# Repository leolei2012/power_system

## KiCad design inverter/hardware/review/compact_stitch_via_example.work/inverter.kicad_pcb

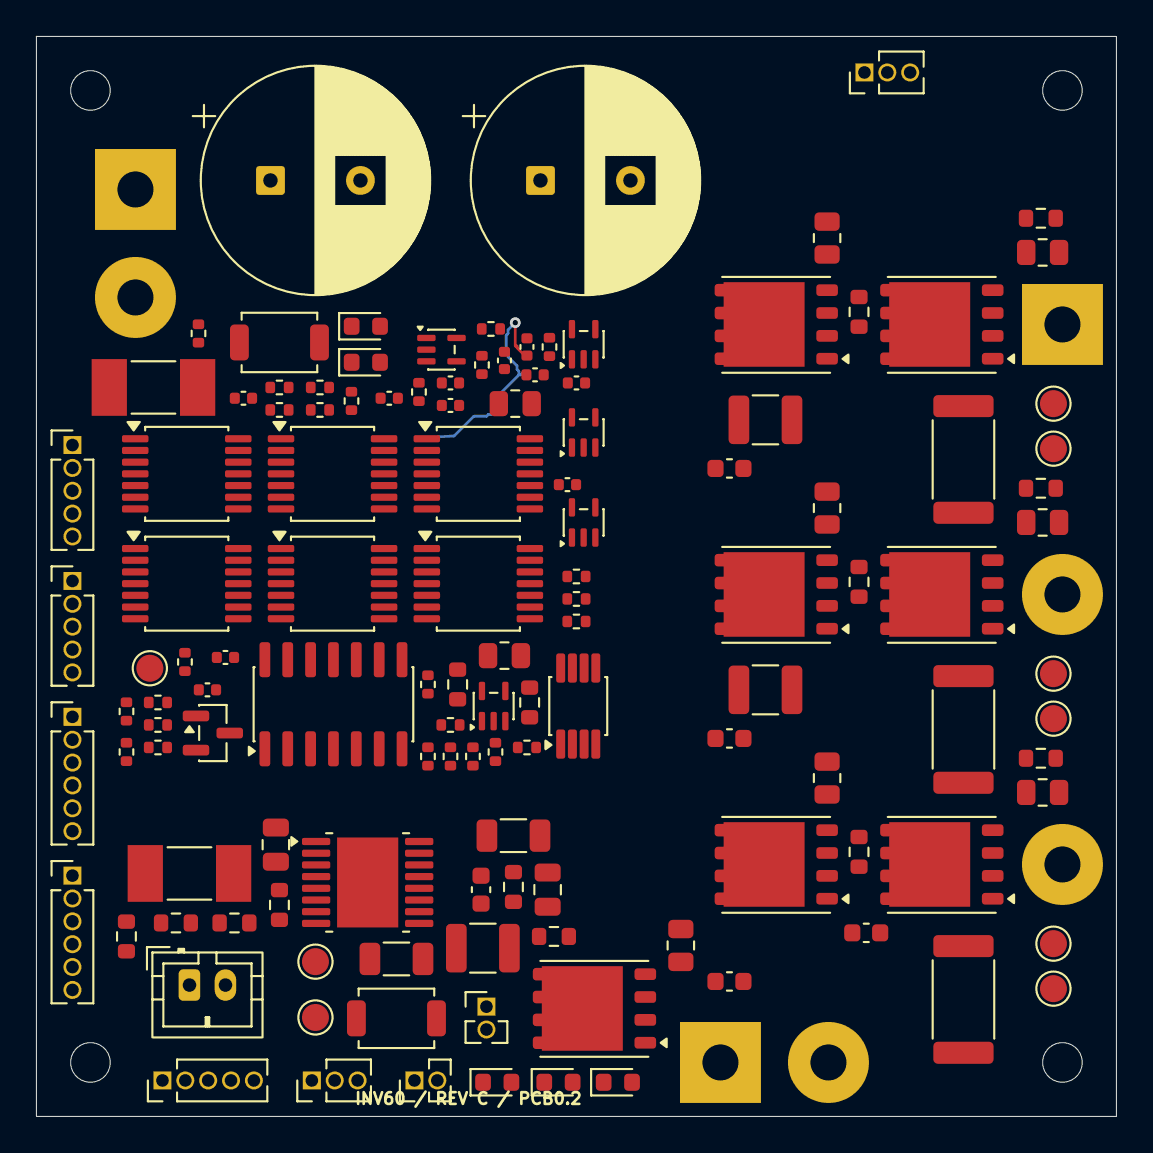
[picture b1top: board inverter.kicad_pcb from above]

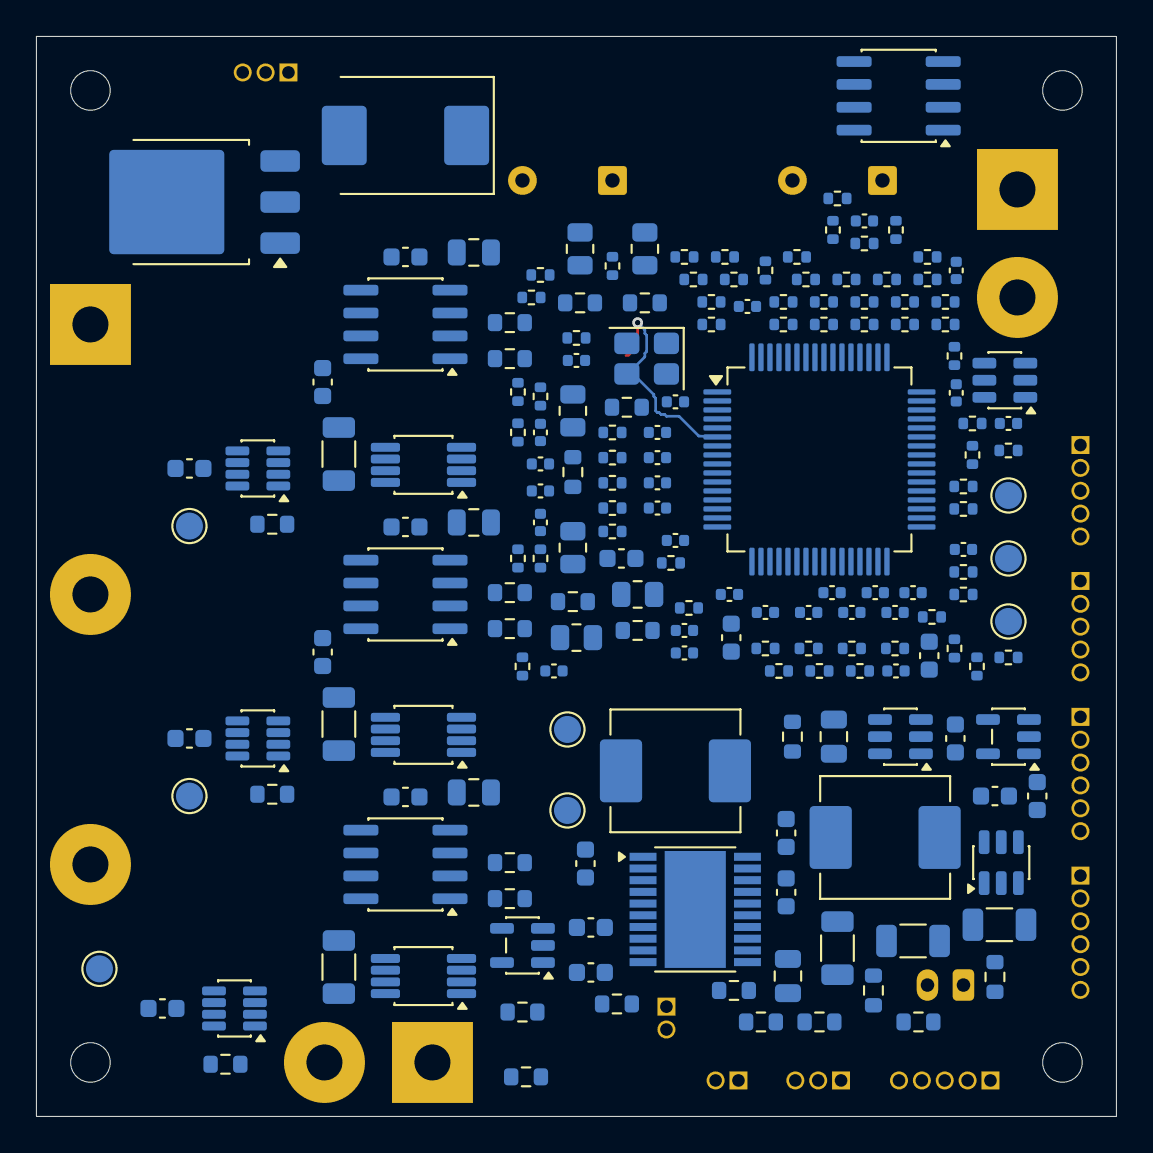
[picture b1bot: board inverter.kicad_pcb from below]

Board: 6 copper layers, 60.0 x 60.0 mm, 317 parts (183 on the bottom side), 209 nets.

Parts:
C1: 1u; C_0805_2012Metric
C2: 22n; C_0603_1608Metric
C3, C6, C11: 10u; C_1206_3216Metric
C4, C5, C9, C12, C24, C26, C28, C30, C32, C34, C36, C37, C38, C39, C51, C52, C53: 100n; C_0603_1608Metric
C7: 470n; C_0805_2012Metric
C8: 22u; C_1210_3225Metric
C10, C27, C31, C35: 4.7u; C_0805_2012Metric
C13, C14: 22u; C_1206_3216Metric
C15, C23, C78, C80: 1u; C_0603_1608Metric
C16: 2.2u; C_0603_1608Metric
C17, C40, C41, C43, C45, C47, C49, C54, C56, C57, C58, C59, C60, C61, C62, C63, C64, C65, C66, C67, C77, C79, C81, C82: 100n; C_0402_1005Metric
C18: 10u; C_0805_2012Metric
C19, C20: 220u / 100V; CP_Radial_D12.5mm_H25mm_P5.00mm
C21, C22: 2.2u / 100V X7R; C_1210_3225Metric
C25, C29, C33: 2.2u; C_1206_3216Metric
C42: 100p; C_0402_1005Metric
C44, C46, C48, C69, C70, C71, C72, C73, C74, C75, C76: 1n; C_0402_1005Metric
C50, C55: 10n; C_0402_1005Metric
C68: 4.7u; C_0603_1608Metric
C83, C84: 18p / provisional; C_0402_1005Metric
D1: MBRD20150CT-13; TO-252-3_TabPin2
D2: SMCJ60CA / CANDIDATE DNP; D_SMC
D3: PWR; LED_0603_1608Metric
D4: LED_RUN; LED_0603_1608Metric
D5: LED_FAULT; LED_0603_1608Metric
D6: LED_COMM; LED_0603_1608Metric
D7: LED_AUX; LED_0603_1608Metric
F1: 0476015.MRSN; Fuse_Littelfuse-NANO2-451_453
F2: 0451002.MRL; Fuse_Littelfuse-NANO2-451_453
H1, H2, H3, H4: MountingHole_2.2mm_M2
J2: AUX: +12..24V / GND; JST_PH_B2B-PH-K_1x02_P2.00mm_Vertical
J3: DC INPUT: + / -; WireSolder_2P_P6.00mm_D2.00mm
J4: RAW PWM: U / V / W; WireSolder_3P_P15.00mm_D2.00mm
J5: BRAKE POWER: BR+ / BR_SW; WireSolder_2P_P6.00mm_D2.00mm
J7: OPTIONAL SENSOR 5V / GND; PinHeader_HCTL_PZ127_1x02_P1.27mm_D0.70mm
J8: EXTERNAL 10k NTC; PinHeader_HCTL_PZ127_1x02_P1.27mm_D0.70mm
J9: ENC_A: PWR GND A B Z; PinHeader_HCTL_PZ127_1x05_P1.27mm_D0.70mm
J10: ENC_B: PWR GND A B Z; PinHeader_HCTL_PZ127_1x05_P1.27mm_D0.70mm
J11: SPI_A: PWR GND SCK MOSI MISO CS; PinHeader_HCTL_PZ127_1x06_P1.27mm_D0.70mm
J12: SPI_B: PWR GND SCK MOSI MISO CS; PinHeader_HCTL_PZ127_1x06_P1.27mm_D0.70mm
J13: SWD: VTREF IO CLK GND NRST; PinHeader_HCTL_PZ127_1x05_P1.27mm_D0.70mm
J14: TTL: TX RX GND; PinHeader_HCTL_PZ127_1x03_P1.27mm_D0.70mm
J15: CAN: H L GND; PinHeader_HCTL_PZ127_1x03_P1.27mm_D0.70mm
L1, L2: 4.7uH; L_Sunlord_MWSA0603S
Q1, Q2, Q3, Q4, Q5, Q6, Q7: BSC110N15NS5; BSC110N15NS5_TDSON8_8PhysicalPins
Q8: MMBT3904LT1G; SOT-23
R1: 78.7k; R_0603_1608Metric
R2, R4, R7, R10, R11, R15, R16, R18, R21, R22, R23, R24, R27, R28, R29, R30, R33, R34, R35, R36, R50, R51, R55, R56, R60, R61, R65, R66: 10k; R_0603_1608Metric
R3: 221k; R_0603_1608Metric
R5: 402k; R_0603_1608Metric
R6: 7.87k; R_0603_1608Metric
R8, R9: 100k; R_0603_1608Metric
R12: 20k; R_0603_1608Metric
R13, R40, R41, R44, R45, R70, R72, R73, R74, R76, R77, R78, R79, R80, R81, R82, R95, R97, R99, R102, R104, R106, R112, R118, R122, R125, R128, R143: 10k; R_0402_1005Metric
R14: 49.9k; R_0603_1608Metric
R17, R19, R20, R25, R26, R31, R32: 15; R_0805_2012Metric
R37, R38, R39: 47; R_0603_1608Metric
R42, R47: 39k; R_0402_1005Metric
R43, R46: 1.8k; R_0402_1005Metric
R48, R49, R53, R54, R58, R59, R63, R64: 240k; R_0805_2012Metric
R52, R57, R62, R67: 47; R_0402_1005Metric
R68: 20k; R_0402_1005Metric
R69: 13k; R_0402_1005Metric
R71: 76.1k; R_0402_1005Metric
R75, R83: 100k; R_0402_1005Metric
R84, R85, R86, R87, R88, R89, R90, R91, R94, R96, R98, R101, R103, R105, R124: 100; R_0402_1005Metric
R92, R93, R100, R107, R113, R119, R126, R127: 0; R_0402_1005Metric
R108, R109, R110, R111, R114, R115, R116, R117, R120, R121, R123, R135, R136, R137, R138, R139, R140, R141, R142: 33; R_0402_1005Metric
R129: 120; R_0402_1005Metric
R130, R131, R132, R133, R134: 2.2k; R_0402_1005Metric
RS1, RS2, RS3: 5m / 3W / 1%; R_2512_6332Metric
SW1: AUX_RESET; SW_SPST_TS-1088-xR020
SW2: MCU_RESET; SW_SPST_TS-1088-xR020
TP1: +12V_DRV; TestPoint_Pad_D1.5mm
TP2: BB_VREG; TestPoint_Pad_D1.5mm
TP3: DRV_PG_LOGIC; TestPoint_Pad_D1.5mm
TP4: SENSOR_PWR_FLT_N; TestPoint_Pad_D1.5mm
TP5: U_PHASE; TestPoint_Pad_D1.5mm
TP6: U_SOURCE; TestPoint_Pad_D1.5mm
TP7: V_PHASE; TestPoint_Pad_D1.5mm
TP8: V_SOURCE; TestPoint_Pad_D1.5mm
TP9: W_PHASE; TestPoint_Pad_D1.5mm
TP10: W_SOURCE; TestPoint_Pad_D1.5mm
TP11: I_U; TestPoint_Pad_D1.5mm
TP12: I_V; TestPoint_Pad_D1.5mm
TP13: I_W; TestPoint_Pad_D1.5mm
TP14: FAULT_LATCH; TestPoint_Pad_D1.5mm
TP15: BOOT0; TestPoint_Pad_D1.5mm
TP16: FAULT_N; TestPoint_Pad_D1.5mm
TP17: ENABLE_IN; TestPoint_Pad_D1.5mm
U1: TPS26600PWPR; HTSSOP-16-1EP_4.4x5mm_P0.65mm_EP3.4x5mm_Mask2.66x2.46mm
U2: TPS55165QPWPRQ1; TI_PWP0020W_HTSSOP-20_4.4x6.5mm_P0.65mm_EP2.79x3.64mm
U3: AP63205WU-7; TSOT-23-6
U4: TPS7A2033PDBVR; SOT-23-5
U5: TPS2553QDBVRQ1; SOT-23-6
U6: TPS3808G33DBVR; SOT-23-6
U7, U8, U9: 2ED2182S06FXUMA1; SOIC-8_3.9x4.9mm_P1.27mm
U10, U11, U12: INA241A1IDDFR; SOT-23-8
U13, U14, U15, U16, U17: TLV9001IDCKR; SOT-353_SC-70-5
U18, U19, U20, U21: TLV3202AIDGK; VSSOP-8_3x3mm_P0.65mm
U22, U23, U24, U25, U26: 74LVC08APW,118; TSSOP-14_4.4x5mm_P0.65mm
U27: 74LVC00APW,118; TSSOP-14_4.4x5mm_P0.65mm
U28: 74LVC74AD,118; SOIC-14_3.9x8.7mm_P1.27mm
U29: UCC27517DBVR; SOT-23-5
U30: STM32G431RBT6; LQFP-64_10x10mm_P0.5mm
U31: SN65HVD232DR; SOIC-8_3.9x4.9mm_P1.27mm
Y1: 8MHz / CL TBD / DNP; Crystal_SMD_3225-4Pin_3.2x2.5mm

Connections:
+3V3_A_MCU: C77.1, C78.1, R92.2, R93.1, U30.29
+3V3_INV: C16.1, C17.1, C37.1, C38.1, C39.1, C41.1, C43.1, C45.1, C47.1, C49.1, C51.1, C52.1, C53.1, C54.1, C56.1, C57.1, C58.1, C59.1, C60.1, C61.1, C62.1, C63.1, C64.1, C65.1, C66.1, C67.1, C68.1, C82.1, J13.1, R7.2, R13.2, R15.2, R40.1, R42.1, R45.1, R68.1, R70.1, R92.1, R95.2, R97.2, R99.2, R102.2, R104.2, R106.2, R112.2, R118.2, R125.2, R128.2, R130.1, R131.1, R132.1, R133.1, R134.1, R143.2, U4.5, U6.3, U6.5, U6.6, U10.6, U11.6, U12.6, U13.5, U14.5, U15.5, U16.5, U17.5, U18.8, U19.8, U20.8, U21.8, U22.14, U23.14, U24.14, U25.14, U26.14, U27.14, U28.1, U28.10, U28.13, U28.14, U30.1, U30.16, U30.32, U30.48, U30.64, U31.3
+5V_INV: C13.1, C14.1, C15.1, L2.2, R10.1, U3.1, U4.1, U4.3, U5.1, U5.3
+5V_SENSOR: C18.1, J7.1, R100.1, R107.1, R113.1, R119.1, U5.6
+12V_DRV: C8.1, C9.1, C23.1, C24.1, C27.1, C28.1, C31.1, C32.1, C35.1, C36.1, R71.1, TP1.1, U2.16, U2.17, U7.5, U8.5, U9.5, U29.1
/Analog protection/DRV_UV_DIV: R71.2, R72.1, U21.5
/Auxiliary input/AUX_DVDT: C2.1, U1.12
/Auxiliary input/AUX_FUSED: C1.1, F2.2, R1.1, R3.1, R8.1, U1.1, U1.2
/Auxiliary input/AUX_ILIM: R6.1, U1.11
/Auxiliary input/AUX_IN: F2.1, J2.1
/Auxiliary input/AUX_MODE: R5.1, U1.6
/Auxiliary input/AUX_OV_DIV: R3.2, R4.1, U1.5
/Auxiliary input/AUX_SHDN_N: R8.2, SW1.1, U1.7
/Auxiliary input/AUX_UV_DIV: R1.2, R2.1, U1.3
/Auxiliary input/EFUSE_RTN: C2.2, R2.2, R4.2, R5.2, R6.2, SW1.2, U1.8, U1.17
/Bus and brake/BR_DRV: R17.1, U29.5
/Bus and brake/BR_GATE: Q7.4, R17.2, R18.1
/Bus and brake/BR_SW: J5.2, Q7.5, Q7.6, Q7.7, Q7.8
/Bus and brake/DC_FUSED: D1.1, D1.3, F1.2
/Bus and brake/DC_INPUT_POS: F1.1, J3.1
/Current sensing/OC_HI_MID: R46.2, R47.1
/Current sensing/OC_LO_MID: R42.2, R43.1
/Current sensing/VBIAS_1V65: U10.3, U10.7, U11.3, U11.7, U12.3, U12.7, U13.3, U13.4
/Current sensing/VBIAS_DIV: C40.1, R40.2, R41.1, U13.1
/Debug and communication/CAN_H: J15.1, R129.1, U31.7
/Debug and communication/CAN_L: J15.2, R129.2, U31.6
/Debug and communication/CAN_RX_PHY: R127.1, U31.4
/Debug and communication/CAN_TX_PHY: R126.2, R128.1, U31.1
/Debug and communication/LED_AN_0: D3.2, R130.2
/Debug and communication/LED_AN_1: D4.2, R131.2
/Debug and communication/LED_AN_2: D5.2, R132.2
/Debug and communication/LED_AN_3: D6.2, R133.2
/Debug and communication/LED_AN_4: D7.2, R134.2
/Debug and communication/SWCLK_PORT: J13.3, R121.1
/Debug and communication/SWDIO_PORT: J13.2, R120.1
/Debug and communication/UART_RX_PORT: J14.2, R124.1
/Debug and communication/UART_TX_PORT: J14.1, R123.2
/Driver supply/BB_BST1: C4.1, U2.3
/Driver supply/BB_BST2: C5.1, U2.19
/Driver supply/BB_L1: C4.2, L1.1, U2.2
/Driver supply/BB_L2: C5.2, L1.2, U2.20
/Driver supply/BB_PG_DLY: R9.1, U2.10
/Driver supply/BB_VREG: C10.1, TP2.1, U2.11, U2.12, U2.14
/Driver supply/DRV_PG_NOM: R10.2, R11.1, U2.15
/Encoders and SPI/ENC_A_A_PORT: J9.3, R94.1
/Encoders and SPI/ENC_A_B_PORT: J9.4, R96.1
/Encoders and SPI/ENC_A_VCC: J9.1, R100.2
/Encoders and SPI/ENC_A_Z_PORT: J9.5, R98.1
/Encoders and SPI/ENC_B_A_PORT: J10.3, R101.1
/Encoders and SPI/ENC_B_B_PORT: J10.4, R103.1
/Encoders and SPI/ENC_B_VCC: J10.1, R107.2
/Encoders and SPI/ENC_B_Z_PORT: J10.5, R105.1
/Encoders and SPI/SPI_A_CS_PORT: J11.6, R111.2
/Encoders and SPI/SPI_A_MISO_PORT: J11.5, R110.2
/Encoders and SPI/SPI_A_MOSI_PORT: J11.4, R109.2
/Encoders and SPI/SPI_A_SCK_PORT: J11.3, R108.2
/Encoders and SPI/SPI_A_VCC: J11.1, R113.2
/Encoders and SPI/SPI_B_CS_PORT: J12.6, R117.2
/Encoders and SPI/SPI_B_MISO_PORT: J12.5, R116.2
/Encoders and SPI/SPI_B_MOSI_PORT: J12.4, R115.2
/Encoders and SPI/SPI_B_SCK_PORT: J12.3, R114.2
/Encoders and SPI/SPI_B_VCC: J12.1, R119.2
/Hardware latch/ENABLE_N: U24.10, U27.3
/Hardware latch/FAULT_ACTIVE: R74.1, U27.6
/Hardware latch/FAULT_BASE: Q8.1, R74.2, R75.1
/Hardware latch/FAULT_LATCH: TP14.1, U28.5
/Hardware latch/HEALTH_ALL: U24.6, U24.9, U24.12, U27.4, U28.4
/Hardware latch/HEALTH_CHAIN_1: U22.3, U22.4
/Hardware latch/HEALTH_CHAIN_2: U22.6, U22.9
/Hardware latch/HEALTH_CHAIN_3: U22.8, U22.12
/Hardware latch/HEALTH_CHAIN_4: U22.11, U23.1
/Hardware latch/HEALTH_CHAIN_5: U23.3, U23.4
/Hardware latch/HEALTH_CHAIN_6: U23.6, U23.9
/Hardware latch/HEALTH_CHAIN_7: U23.8, U23.12
/Hardware latch/HEALTH_CHAIN_8: U23.11, U24.1
/Hardware latch/HEALTH_CHAIN_9: U24.3, U24.4
/Hardware latch/HEALTH_UNLATCHED: U24.11, U25.1
/Hardware latch/NO_LATCH: U24.13, U27.5, U28.6
/Hardware latch/RESET_CLK: C55.1, R73.2, U28.3
/Hardware latch/RESET_REQUEST: R73.1, U24.8
/Logic and sensors/BUCK_BST: C12.1, U3.6
/Logic and sensors/BUCK_SW: C12.2, L2.1, U3.5
/Logic and sensors/SENSOR_ILIM: R14.1, U5.5
/Logic and sensors/SENSOR_PWR_FLT_N: R15.1, TP4.1, U5.4
/U half bridge/U_BOOT: C25.1, C26.1, U7.8
/U half bridge/U_GATE_H: Q1.4, R19.2, R21.1
/U half bridge/U_GATE_L: Q2.4, R20.2, R22.1
/U half bridge/U_HO: R19.1, U7.7
/U half bridge/U_LO: R20.1, U7.4
/V half bridge/V_BOOT: C29.1, C30.1, U8.8
/V half bridge/V_GATE_H: Q3.4, R25.2, R27.1
/V half bridge/V_GATE_L: Q4.4, R26.2, R28.1
/V half bridge/V_HO: R25.1, U8.7
/V half bridge/V_LO: R26.1, U8.4
/Voltage and NTC/V_DC_DIV: C42.1, R50.2, R51.1, U14.1
/Voltage and NTC/V_DC_DIV1: R48.2, R49.1
/Voltage and NTC/V_DC_DIV2: R49.2, R50.1
/Voltage and NTC/V_U: R57.1, U15.3, U15.4
/Voltage and NTC/V_U_DIV: C44.1, R55.2, R56.1, U15.1
/Voltage and NTC/V_U_DIV1: R53.2, R54.1
/Voltage and NTC/V_U_DIV2: R54.2, R55.1
/Voltage and NTC/V_V: R62.1, U16.3, U16.4
/Voltage and NTC/V_V_DIV: C46.1, R60.2, R61.1, U16.1
/Voltage and NTC/V_V_DIV1: R58.2, R59.1
/Voltage and NTC/V_V_DIV2: R59.2, R60.1
/Voltage and NTC/V_W: R67.1, U17.3, U17.4
/Voltage and NTC/V_W_DIV: C48.1, R65.2, R66.1, U17.1
/Voltage and NTC/V_W_DIV1: R63.2, R64.1
/Voltage and NTC/V_W_DIV2: R64.2, R65.1
/W half bridge/W_BOOT: C33.1, C34.1, U9.8
/W half bridge/W_GATE_H: Q5.4, R31.2, R33.1
/W half bridge/W_GATE_L: Q6.4, R32.2, R34.1
/W half bridge/W_HO: R31.1, U9.7
/W half bridge/W_LO: R32.1, U9.4
ADC_I_U: C69.1, R84.2, U30.8
ADC_I_V: C70.1, R85.2, U30.9
ADC_I_W: C71.1, R86.2, U30.10
ADC_TEMP_NTC: C76.1, R91.2, U30.26
ADC_V_DC: C72.1, R87.2, U30.11
ADC_V_U: C73.1, R88.2, U30.18
ADC_V_V: C74.1, R89.2, U30.24
ADC_V_W: C75.1, R90.2, U30.25
AUX_FLT_N: R7.1, U1.14, U24.5
AUX_PROTECTED: C3.1, C6.1, C7.1, C11.1, U1.15, U1.16, U2.4, U2.5, U2.6, U3.2, U3.3
BOOT0: R122.1, TP15.1, U30.61
BRAKE_IN: R16.1, R142.2, U29.3
BUS_OV_OK: U21.1, U23.5
CAN_RX: R127.2, U30.45
CAN_TX: R126.1, U30.46
DRIVE_PERMIT: R83.1, U25.3, U25.5, U25.10, U25.13, U26.2, U26.5, U26.10
DRV_PG_LOGIC: R11.2, R12.1, TP3.1, U24.2
DRV_UV_OK: U21.7, U23.10
ENABLE_IN: R82.1, R141.2, TP17.1, U25.2, U27.1, U27.2
ENC_A_A: R94.2, R95.1, U30.12
ENC_A_B: R96.2, R97.1, U30.13
ENC_A_Z: R98.2, R99.1, U30.14
ENC_B_A: R101.2, R102.1, U30.59
ENC_B_B: R103.2, R104.1, U30.60
ENC_B_Z: R105.2, R106.1, U30.17
FAULT_N: Q8.3, R143.1, TP16.1, U30.34
GND: C1.2, C3.2, C6.2, C7.2, C8.2, C9.2, C10.2, C11.2, C13.2, C14.2, C15.2, C16.2, C17.2, C18.2, C19.2, C20.2, C21.2, C22.2, C23.2, C24.2, C37.2, C38.2, C39.2, C40.2, C41.2, C42.2, C43.2, C44.2, C45.2, C46.2, C47.2, C48.2, C49.2, C50.2, C51.2, C52.2, C53.2, C54.2, C55.2, C56.2, C57.2, C58.2, C59.2, C60.2, C61.2, C62.2, C63.2, C64.2, C65.2, C66.2, C67.2, C68.2, C69.2, C70.2, C71.2, C72.2, C73.2, C74.2, C75.2, C76.2, C77.2, C78.2, C79.2, C80.2, C81.2, C82.2, C83.2, C84.2, D2.2, D3.1, J2.2, J3.2, J7.2, J8.2, J9.2, J10.2, J11.2, J12.2, J13.4, J14.3, J15.3, Q7.1, Q7.2, Q7.3, Q8.2, R9.2, R12.2, R14.2, R16.2, R18.2, R41.2, R44.2, R47.2, R51.2, R56.2, R61.2, R66.2, R69.2, R72.2, R75.2, R76.2, R77.2, R78.2, R79.2, R80.2, R81.2, R82.2, R83.2, R122.2, RS1.2, RS2.2, RS3.2, SW2.2, U1.9, U2.1, U2.7, U2.8, U2.9, U2.13, U2.18, U2.21, U3.4, U4.2, U5.2, U6.2, U10.1, U10.2, U10.4, U11.1, U11.2, U11.4, U12.1, U12.2, U12.4, U13.2, U14.2, U15.2, U16.2, U17.2, U18.4, U19.4, U20.4, U21.4, U22.7, U23.7, U24.7, U25.7, U26.7, U26.12, U26.13, U27.7, U27.9, U27.10, U27.12, U27.13, U28.2, U28.7, U28.11, U28.12, U29.2, U29.4, U30.15, U30.27, U30.31, U30.47, U30.63, U31.2, Y1.2, Y1.4
HSE_IN: C83.1, U30.5, Y1.1
HSE_OUT: C84.1, U30.6, Y1.3
I_U: R37.1, TP11.1, U10.5, U18.2, U18.5
I_U_PORT: R37.2, R84.1
I_V: R38.1, TP12.1, U11.5, U19.2, U19.5
I_V_PORT: R38.2, R85.1
I_W: R39.1, TP13.1, U12.5, U20.2, U20.5
I_W_PORT: R39.2, R86.1
LED_AUX: D7.1, U30.58
LED_COMM: D6.1, U30.55
LED_FAULT: D5.1, U30.40
LED_RUN: D4.1, U30.23
LOGIC_POWER_OK: C81.1, J13.5, R13.1, SW2.1, U6.1, U23.13, U30.7
MCU_BRAKE: R142.1, U30.38
MCU_ENABLE: R141.1, U30.22
MCU_PWM_UH: R135.1, U30.42
MCU_PWM_UL: R136.1, U30.35
MCU_PWM_VH: R137.1, U30.43
MCU_PWM_VL: R138.1, U30.36
MCU_PWM_WH: R139.1, U30.44
MCU_PWM_WL: R140.1, U30.37
OC_HIGH_REF: R45.2, R46.1, U18.3, U19.3, U20.3
OC_LOW_REF: R43.2, R44.1, U18.6, U19.6, U20.6
OC_U_HIGH_OK: U18.1, U22.1
OC_U_LOW_OK: U18.7, U22.2
OC_V_HIGH_OK: U19.1, U22.5
OC_V_LOW_OK: U19.7, U22.10
OC_W_HIGH_OK: U20.1, U22.13
OC_W_LOW_OK: U20.7, U23.2
OV_REF_1V30: R68.2, R69.1, U21.3, U21.6
PWM_UH_IN: R76.1, R135.2, U25.4
PWM_UL_IN: R77.1, R136.2, U25.9
PWM_VH_IN: R78.1, R137.2, U25.12
PWM_VL_IN: R79.1, R138.2, U26.1
PWM_WH_IN: R80.1, R139.2, U26.4
PWM_WL_IN: R81.1, R140.2, U26.9
SPI_A_CS: R111.1, R112.1, U30.51
SPI_A_MISO: R110.1, U30.20
SPI_A_MOSI: R109.1, U30.21
SPI_A_SCK: R108.1, U30.19
SPI_B_CS: R117.1, R118.1, U30.41
SPI_B_MISO: R116.1, U30.53
SPI_B_MOSI: R115.1, U30.54
SPI_B_SCK: R114.1, U30.52
SWCLK: R121.2, U30.50
SWDIO: R120.2, U30.49
TEMP_NTC: C50.1, J8.1, R70.2, R91.1
UART_RX: R124.2, R125.1, U30.33
UART_TX: R123.1, U30.30
U_HIN: R23.1, U7.1, U25.6
U_LIN: R24.1, U7.2, U25.8
U_PHASE: C25.2, C26.2, J4.1, Q1.1, Q1.2, Q1.3, Q2.5, Q2.6, Q2.7, Q2.8, R21.2, R53.1, TP5.1, U7.6
U_SOURCE: C27.2, C28.2, Q2.1, Q2.2, Q2.3, R22.2, R23.2, R24.2, RS1.1, TP6.1, U7.3, U10.8
VBUS: C19.1, C20.1, C21.1, C22.1, D1.2, D2.1, J5.1, Q1.5, Q1.6, Q1.7, Q1.8, Q3.5, Q3.6, Q3.7, Q3.8, Q5.5, Q5.6, Q5.7, Q5.8, R48.1
VREF_MCU: C79.1, C80.1, R93.2, U30.28
V_DC: R52.1, U14.3, U14.4, U21.2
V_DC_PORT: R52.2, R87.1
V_HIN: R29.1, U8.1, U25.11
V_LIN: R30.1, U8.2, U26.3
V_PHASE: C29.2, C30.2, J4.2, Q3.1, Q3.2, Q3.3, Q4.5, Q4.6, Q4.7, Q4.8, R27.2, R58.1, TP7.1, U8.6
V_SOURCE: C31.2, C32.2, Q4.1, Q4.2, Q4.3, R28.2, R29.2, R30.2, RS2.1, TP8.1, U8.3, U11.8
V_U_PORT: R57.2, R88.1
V_V_PORT: R62.2, R89.1
V_W_PORT: R67.2, R90.1
W_HIN: R35.1, U9.1, U26.6
W_LIN: R36.1, U9.2, U26.8
W_PHASE: C33.2, C34.2, J4.3, Q5.1, Q5.2, Q5.3, Q6.5, Q6.6, Q6.7, Q6.8, R33.2, R63.1, TP9.1, U9.6
W_SOURCE: C35.2, C36.2, Q6.1, Q6.2, Q6.3, R34.2, R35.2, R36.2, RS3.1, TP10.1, U9.3, U12.8

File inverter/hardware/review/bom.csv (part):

Reference,Value,Quantity,DNP,Sheet,Manufacturer,MPN,Supplier_PN,Purchase_URL,Footprint,Voltage_Rating,Tolerance,Design_Note,Selection_Status,Verification
C1,1u,1,no,/Auxiliary input/,YAGEO,TBD,,,Capacitor_SMD:C_0805_2012Metric,100V,,,value assigned; DC bias/MPN/LCSC pending,
C2,22n,1,no,/Auxiliary input/,YAGEO,TBD,,,Capacitor_SMD:C_0603_1608Metric,25V,,,value assigned; DC bias/MPN/LCSC pending,
C3,10u,1,no,/Auxiliary input/,YAGEO,TBD,,,Capacitor_SMD:C_1206_3216Metric,50V,,,value assigned; DC bias/MPN/LCSC pending,
F2,0451002.MRL,1,no,/Auxiliary input/,Littelfuse,0451002.MRL,C99547,https://item.szlcsc.com/100761.html,MyFootprints:Littelfuse_NANO2_451_476_Pad1.96x3.15mm_Gap2.95mm,,,,"Exact 2 A candidate fits current Nano2 451/453 footprint; converter inrush, short-circuit coordination and ambient derating remain application checks.",reviewed
J2,AUX: +12..24V / GND,1,no,/Auxiliary input/,JST,B2B-PH-K-S(LF)(SN),C131337,https://item.szlcsc.com/142630.html,MyFootprints:JST_PH_B2B-PH-K_1x02_P2.00mm_Vertical,,,,compact mechanical engineering candidate; original pin order retained,reviewed
R1,78.7k,1,no,/Auxiliary input/,YAGEO,TBD,,,Resistor_SMD:R_0603_1608Metric,,0.1%,,value assigned; exact MPN/LCSC pending,
R2,10k,1,no,/Auxiliary input/,YAGEO,TBD,,,Resistor_SMD:R_0603_1608Metric,,0.1%,,value assigned; exact MPN/LCSC pending,
R3,221k,1,no,/Auxiliary input/,YAGEO,TBD,,,Resistor_SMD:R_0603_1608Metric,,0.1%,,value assigned; exact MPN/LCSC pending,
R4,10k,1,no,/Auxiliary input/,YAGEO,TBD,,,Resistor_SMD:R_0603_1608Metric,,0.1%,,value assigned; exact MPN/LCSC pending,
R5,402k,1,no,/Auxiliary input/,YAGEO,TBD,,,Resistor_SMD:R_0603_1608Metric,,1%,402k selects current-limit latch-off; direct RTN would select auto-retry,value assigned; exact MPN/LCSC pending,
R6,7.87k,1,no,/Auxiliary input/,YAGEO,TBD,,,Resistor_SMD:R_0603_1608Metric,,1%,Nominal 11.8k/R -> 1.50 A; tolerance/SOA/startup review,value assigned; exact MPN/LCSC pending,
R7,10k,1,no,/Auxiliary input/,YAGEO,TBD,,,Resistor_SMD:R_0603_1608Metric,,1%,,value assigned; exact MPN/LCSC pending,
R8,100k,1,yes,/Auxiliary input/,YAGEO,TBD,,,Resistor_SMD:R_0603_1608Metric,,1%,"DNP: remove external 12..24V SHDN pullup. TPS26600 internal SHDN bias is nominal 2.7V, recommended SHDN 0..4V. SW1 still pulls to EFUSE_RTN.","compact revision electrical correction; retain footprint, do not populate",
SW1,AUX_RESET,1,no,/Auxiliary input/,XUNPU,TS-1088-AR02016,C720477,https://item.szlcsc.com/763484.html,MyFootprints:SW_SPST_TS-1088-xR020,,,,Exact small SMD normally-open momentary 2-terminal switch; standard local footprint matches current manufacturer drawing. SW1 bias condition below remains an electrical-review hold point.,reviewed
U1,TPS26600PWPR,1,no,/Auxiliary input/,TI,TPS26600PWPR,C544399,https://item.szlcsc.com/565050.html,MyFootprints:HTSSOP-16-1EP_4.4x5mm_P0.65mm_EP3.4x5mm_Mask2.66x2.46mm,,,,,reviewed
C4,100n,1,no,/Driver supply/,YAGEO,CC0603KRX7R9BB104,C14663,https://item.szlcsc.com/15331.html,MyFootprints:C_0603_1608Metric,50V,10%,,C14663; 50V X7R covers original 25V local decoupling/bootstrap requirement; application transient and DC-bias verification pending,reviewed
C5,100n,1,no,/Driver supply/,YAGEO,CC0603KRX7R9BB104,C14663,https://item.szlcsc.com/15331.html,MyFootprints:C_0603_1608Metric,50V,10%,,C14663; 50V X7R covers original 25V local decoupling/bootstrap requirement; application transient and DC-bias verification pending,reviewed
C6,10u,1,no,/Driver supply/,YAGEO,TBD,,,Capacitor_SMD:C_1206_3216Metric,50V,,,value assigned; DC bias/MPN/LCSC pending,
C7,470n,1,no,/Driver supply/,YAGEO,TBD,,,Capacitor_SMD:C_0805_2012Metric,50V,,,value assigned; DC bias/MPN/LCSC pending,
C8,22u,1,no,/Driver supply/,YAGEO,TBD,,,Capacitor_SMD:C_1210_3225Metric,25V,,,value assigned; DC bias/MPN/LCSC pending,
C9,100n,1,no,/Driver supply/,YAGEO,CC0603KRX7R9BB104,C14663,https://item.szlcsc.com/15331.html,MyFootprints:C_0603_1608Metric,50V,10%,,C14663; 50V X7R covers original 25V local decoupling/bootstrap requirement; application transient and DC-bias verification pending,reviewed
C10,4.7u,1,no,/Driver supply/,YAGEO,TBD,,,Capacitor_SMD:C_0805_2012Metric,10V,,,value assigned; DC bias/MPN/LCSC pending,
L1,4.7uH,1,no,/Driver supply/,Sunlord,MWSA0603S-4R7MT,C408447,https://so.szlcsc.com/global.html?k=MWSA0603S-4R7MT,MyFootprints:L_Sunlord_MWSA0603S,,,,"Meets requested nominal L, current-table and DCR targets; auxiliary-converter operating/thermal qualification pending.",reviewed
R9,100k,1,no,/Driver supply/,YAGEO,TBD,,,Resistor_SMD:R_0603_1608Metric,,1%,,value assigned; exact MPN/LCSC pending,
R10,10k,1,no,/Driver supply/,YAGEO,TBD,,,Resistor_SMD:R_0603_1608Metric,,1%,,value assigned; exact MPN/LCSC pending,
R11,10k,1,no,/Driver supply/,YAGEO,TBD,,,Resistor_SMD:R_0603_1608Metric,,1%,,value assigned; exact MPN/LCSC pending,
R12,20k,1,no,/Driver supply/,YAGEO,TBD,,,Resistor_SMD:R_0603_1608Metric,,1%,,value assigned; exact MPN/LCSC pending,
TP1,+12V_DRV,1,no,/Driver supply/,,,,,TestPoint:TestPoint_Pad_D1.5mm,,,,,
TP2,BB_VREG,1,no,/Driver supply/,,,,,TestPoint:TestPoint_Pad_D1.5mm,,,,,
TP3,DRV_PG_LOGIC,1,no,/Driver supply/,,,,,TestPoint:TestPoint_Pad_D1.5mm,,,,,
U2,TPS55165QPWPRQ1,1,no,/Driver supply/,TI,TPS55165QPWPRQ1,C2071629,https://item.szlcsc.com/2163212.html,MyFootprints:TI_PWP0020W_HTSSOP-20_4.4x6.5mm_P0.65mm_EP2.79x3.64mm,,,,,reviewed
C11,10u,1,no,/Logic and sensors/,YAGEO,TBD,,,Capacitor_SMD:C_1206_3216Metric,50V,,,value assigned; DC bias/MPN/LCSC pending,
C12,100n,1,no,/Logic and sensors/,YAGEO,CC0603KRX7R9BB104,C14663,https://item.szlcsc.com/15331.html,MyFootprints:C_0603_1608Metric,50V,10%,,C14663; 50V X7R covers original 25V local decoupling/bootstrap requirement; application transient and DC-bias verification pending,reviewed
C13,22u,1,no,/Logic and sensors/,YAGEO,TBD,,,Capacitor_SMD:C_1206_3216Metric,16V,,,value assigned; DC bias/MPN/LCSC pending,
C14,22u,1,no,/Logic and sensors/,YAGEO,TBD,,,Capacitor_SMD:C_1206_3216Metric,16V,,,value assigned; DC bias/MPN/LCSC pending,
C15,1u,1,no,/Logic and sensors/,YAGEO,TBD,,,Capacitor_SMD:C_0603_1608Metric,25V,,,value assigned; DC bias/MPN/LCSC pending,
C16,2.2u,1,no,/Logic and sensors/,YAGEO,TBD,,,Capacitor_SMD:C_0603_1608Metric,25V,,,value assigned; DC bias/MPN/LCSC pending,
C17,100n,1,no,/Logic and sensors/,YAGEO,TBD,,,Capacitor_SMD:C_0402_1005Metric,25V,,,value assigned; DC bias/MPN/LCSC pending,
C18,10u,1,no,/Logic and sensors/,YAGEO,TBD,,,Capacitor_SMD:C_0805_2012Metric,16V,,,value assigned; DC bias/MPN/LCSC pending,
J7,OPTIONAL SENSOR 5V / GND,1,yes,/Logic and sensors/,HCTL,PZ127-1-02-Z,C5372825,https://item.szlcsc.com/6225189.html,MyFootprints:HCTL_PZ127_1x02_P1.27mm_Drill0.70mm,,,,compact mechanical engineering candidate; original pin order retained,reviewed
L2,4.7uH,1,no,/Logic and sensors/,Sunlord,MWSA0603S-4R7MT,C408447,https://so.szlcsc.com/global.html?k=MWSA0603S-4R7MT,MyFootprints:L_Sunlord_MWSA0603S,,,,"Meets requested nominal L, current-table and DCR targets; auxiliary-converter operating/thermal qualification pending.",reviewed
R13,10k,1,no,/Logic and sensors/,YAGEO,TBD,,,Resistor_SMD:R_0402_1005Metric,,1%,,value assigned; exact MPN/LCSC pending,
R14,49.9k,1,no,/Logic and sensors/,YAGEO,TBD,,,Resistor_SMD:R_0603_1608Metric,,1%,~0.475..0.582 A datasheet min/max formula at nominal R; resistor tolerance adds error,value assigned; exact MPN/LCSC pending,
R15,10k,1,no,/Logic and sensors/,YAGEO,TBD,,,Resistor_SMD:R_0603_1608Metric,,1%,,value assigned; exact MPN/LCSC pending,
TP4,SENSOR_PWR_FLT_N,1,no,/Logic and sensors/,,,,,TestPoint:TestPoint_Pad_D1.5mm,,,,,
U3,AP63205WU-7,1,no,/Logic and sensors/,Diodes,AP63205WU-7,C2071056,https://item.szlcsc.com/2162639.html,MyFootprints:TSOT-23-6,,,,,reviewed
U4,TPS7A2033PDBVR,1,no,/Logic and sensors/,TI,TPS7A2033PDBVR,C2862740,https://item.szlcsc.com/3067417.html,MyFootprints:SOT-23-5,,,,,reviewed
U5,TPS2553QDBVRQ1,1,no,/Logic and sensors/,TI,TPS2553QDBVRQ1,C130055,https://item.szlcsc.com/141342.html,MyFootprints:SOT-23-6,,,,,reviewed
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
